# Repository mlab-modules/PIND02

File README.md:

# PIND02 - Solid-state semiconductor radiation detector

The PIN diode semiconductor detector for ionizing radiation. 

## Main features
  - sensitivity to a wide range of ionizing radiation types (charged particles, ions, photons, etc.)
  - Low-power consumtion
  - lightweight

## Basic usage

The module outputs pulses, which need to be digitized for computer processing. The suitable hardware for that task is [PCRD07](https://github.com/mlab-modules/PCRD07)

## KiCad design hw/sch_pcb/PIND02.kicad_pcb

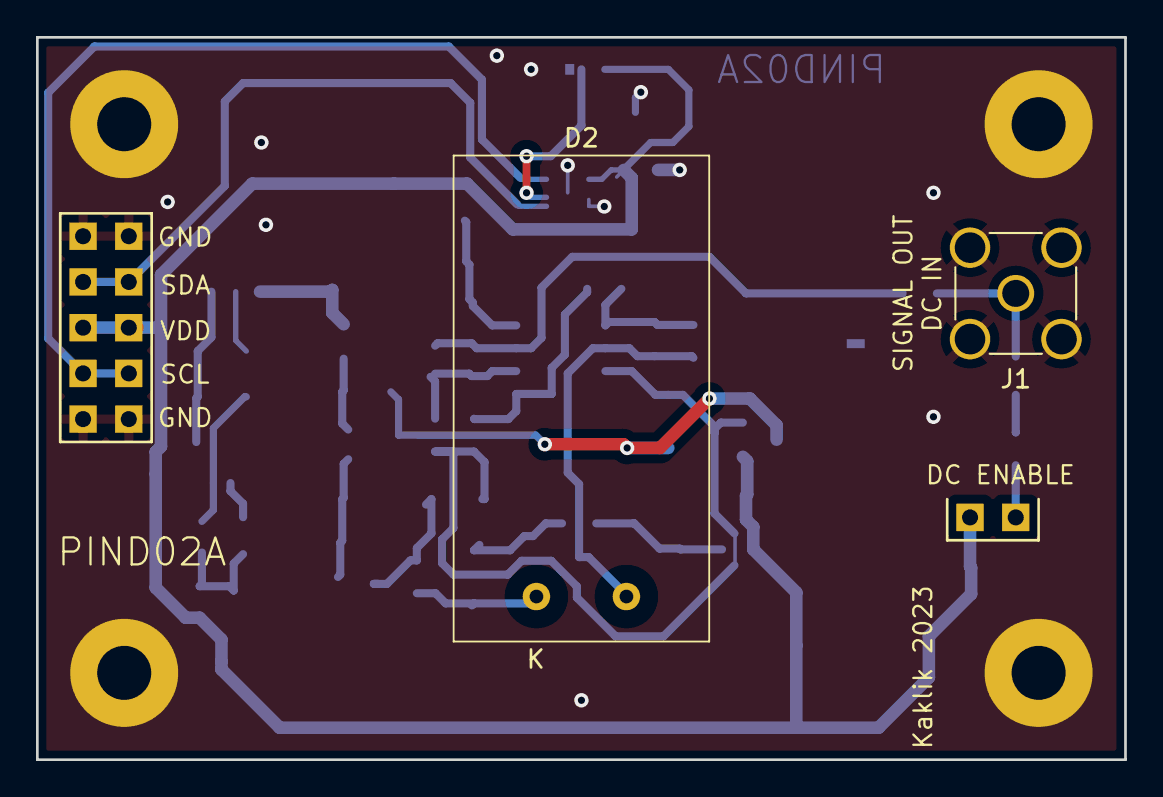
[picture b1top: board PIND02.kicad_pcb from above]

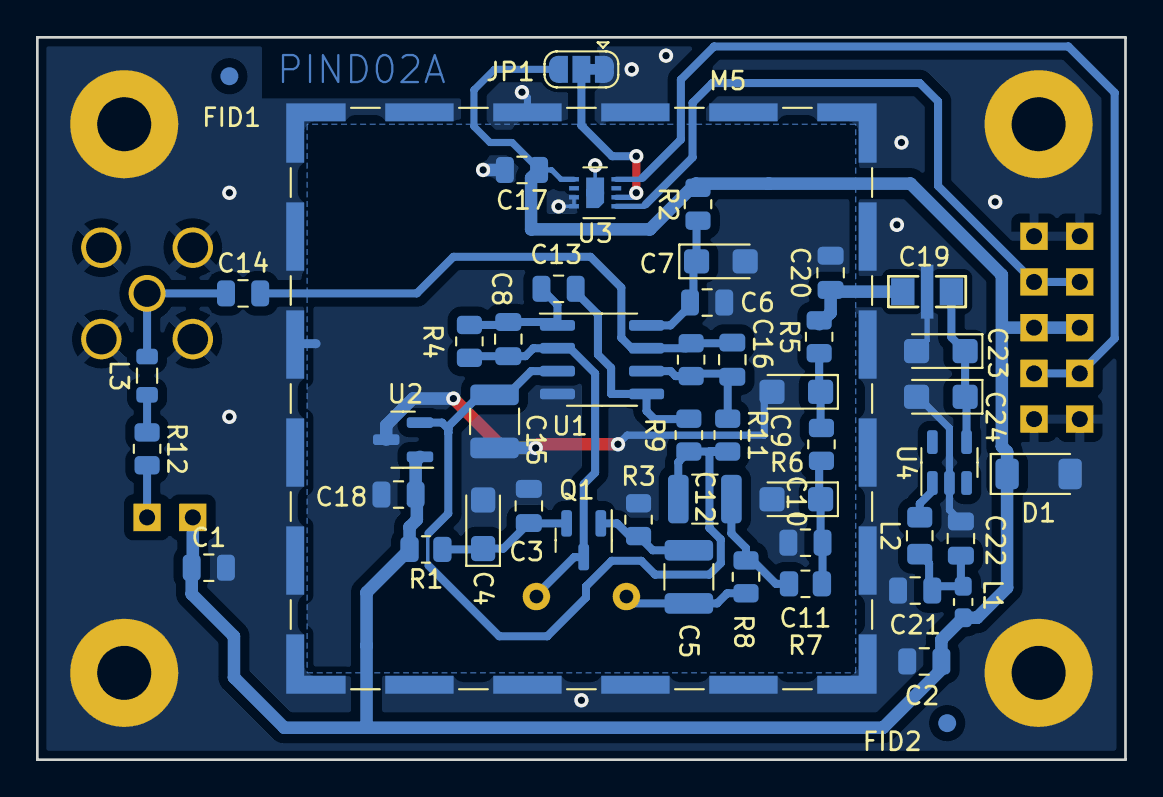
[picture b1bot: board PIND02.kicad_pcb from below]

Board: 2 copper layers, 60.5 x 40.1 mm, 58 parts (50 on the bottom side), 26 nets.

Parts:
C1, C21: 10uF; C_0805_2012Metric
C2, C3, C6, C11, C13, C14, C17, C18, C20, C22: 100nF; C_0805_2012Metric
C4, C7, C9, C10, C23, C24: 10uF; CP_EIA-3216-18_Kemet-A
C5, C12, C15: 1uF; C_1210_3225Metric
C8: 1pF/NP0 251R15S1R0AV4E; C_0805_2012Metric
C16: 3n3; C_0805_2012Metric
C19: NFM21PC105-1uF; FIR_0805
D1: BZV55C-6,2V; D_MiniMELF
D2: S2744-09; HAMAMATSU_S2744-09
FID1, FID2: Fiducial; Fiducial_1mm_Mask2mm
J1: Conn_Coaxial; SMA_Amphenol_901-144_Vertical
J2: MLAB I2C interface; Straight_2x05
J3: HEADER_2x01; Straight_2x01
JP1: Address select; SolderJumper-3_P1.3mm_Bridged12_RoundedPad1.0x1.5mm
JP2: Jumper_2_Bridged; NetTie-2_SMD_Pad0.5mm
L1: NL03KT330; L_0603_1608Metric_Pad1.05x0.95mm_HandSolder
L2: DFE252012P-4R7M; L_0805_2012Metric_Pad1.15x1.40mm_HandSolder
L3: L; L_0805_2012Metric
M1, M2: HOLE M3; MountingHole_3mm
M3, M4: HOLE; MountingHole_3mm
M5: RFShield_TwoPieces; Laird_Technologies_BMI-S-204-F_32.00x32.00mm
Q1: 2SK2394-6; SOT-23
R1, R2: 470R; R_0805_2012Metric
R3, R5, R6, R7, R8, R10: 4k7; R_0805_2012Metric
R4: 10M; R_0805_2012Metric
R9: 10k; R_0805_2012Metric
R11: 1k; R_0805_2012Metric
R12: 100; R_0805_2012Metric
U1: OPA2314; SOIC-8_3.9x4.9mm_P1.27mm
U2: ISL21080DIH312Z-TK; SOT-23
U3: SHT31-DIS; Sensirion_DFN-8-1EP_2.5x2.5mm_P0.5mm_EP1.1x1.7mm
U4: TPS613222ADBV; SOT-23-5

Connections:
+5V: C19.3, C20.1, R5.2
/A: C8.2, D2.2 (A), Q1.3 (G), R4.2, U1.2 (-)
/K: C5.2, D2.1 (K), R8.1
/REF: C12.2, C15.1, R9.1, R11.2, U1.3 (+), U2.2 (Vout)
GND: C1.2, C2.2, C17.2, C19.2, C21.2, C22.2, C23.2, C24.2, D1.2 (A), J1.2 (Ext), J2.1, J2.2, J2.9, J2.10, JP1.1 (A), JP2.2, M1.1, M2.1, M3.1, M4.1, M5.1 (Shield), U3.7 (R), U3.8 (VSS), U3.9 (VSS), U4.2 (GND)
GNDA: C3.2, C4.2, C6.2, C7.2, C9.2, C10.2, C11.2, C15.2, C18.2, C20.2, JP2.1, R3.2, U1.4 (V-), U2.3 (GND)
unnamed: C9.1, R5.1, R6.2
unnamed: C10.1, C11.1, R6.1, R7.2
unnamed: C12.1, R7.1, R8.2
unnamed: C8.1, C13.2, R4.1, U1.1
unnamed: C14.2, C16.1, R10.1, U1.7
unnamed: C21.1, C22.1, L1.2, L2.1
unnamed: C14.1, J1.1 (In), L3.2
unnamed: J3.2, R12.2
unnamed: JP1.2 (C), U3.2 (ADDR)
unnamed: L3.1, R12.1
unnamed: C3.1, C4.1, Q1.2 (D), R1.1
unnamed: C5.1, Q1.1 (S), R3.1
unnamed: C13.1, R9.2, U1.5 (+)
unnamed: C16.2, R10.2, R11.1, U1.6 (-)
unnamed: C6.1, C7.1, R2.1, U1.8 (V+)
unnamed: J2.7, J2.8, U3.4 (SCL)
unnamed: J2.3, J2.4, U3.1 (SDA)
unnamed: L2.2, U4.1 (SW)
unnamed: C19.1, C23.1, C24.1, U4.4 (VOUT)
VDD: C1.1, C2.1, C17.1, C18.1, D1.1 (K), J2.5, J2.6, J3.1, JP1.3 (B), L1.1, R1.2, R2.2, U2.1 (Vin), U3.5 (VDD)

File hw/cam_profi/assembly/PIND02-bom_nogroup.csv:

Component,Description,Part,References,Value,Footprint,Quantity Per PCB,Datasheet,ust_id
1,Unpolarized capacitor,C,C16,3n3,C_0603_1608Metric,1,~,628d0fc8dc56076e9a223574
2,Unpolarized capacitor,C,C3C6C11C13C14C18,100nF,C_0603_1608Metric,6,~,5c70984812875079b91f8bf2
3,,C_Small-Device-ISM02A-rescue,C2C17,100nF,C_0805_2012Metric,2,,5c70984812875079b91f8bf2
4,,C-device-DATALOGGER01A-rescue-CCP2019V01A-rescue,C20C22,100nF,C_0603_1608Metric,2,,5c70984812875079b91f8bf2
5,Unpolarized capacitor,C,C5C12C15,1uF,C_0603_1608Metric,3,~,643f03ef76c82a1d3b576bed
6,,C_Small-Device-ISM02A-rescue,C1,10uF,C_0805_2012Metric,1,,5c70984812875079b91f8bbe
7,Unpolarized capacitor,C,C4C7C9C10C21,10uF,C_0603_1608Metric,5,~,643f075476c82a1d3b576c19
8,,C-device-DATALOGGER01A-rescue-CCP2019V01A-rescue,C23C24,10uF,C_0603_1608Metric,2,,643f075476c82a1d3b576c19
9,Unpolarized capacitor,C,C8,1pF/NP0 251R15S1R0AV4E,C_0805_2012Metric,1,~,5c70984712875079b91f8b9f
10,,EMI_Filter_C-device-DATALOGGER01A-rescue-CCP2019V01A-rescue,C19,NFM21PC105-1uF,FIR_0805,1,http://www.murata.com/~/media/webrenewal/support/library/cat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,5c70984412875079b91f880f
11,,D_ZENER-MLAB_D,D1,"BZV55C-5,6V",D_SMA,1,,5c70984512875079b91f88b2
12,Photodiode,D_Photo,D2,S2744-09,HAMAMATSU_S2744-09,1,https://www.hamamatsu.com/content/dam/hamamatsu-photonics/si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,628d118cdc56076e9a2235e4
13,"coaxial connector (BNC, SMA, SMB, SMC, Cinch/RCA, LEMO, ...)",Conn_Coaxial,J1,Conn_Coaxial,,1, ~,
14,2x01 2.54 mm pitch header,HEADER_2x01,J3,HEADER_2x01,,1,,
15,"2x05 2.54 mm pitch header, 2 pins next to each other are connected",HEADER_2x05_PARALLEL,J2,HEADER_2x05_PARALLEL,,1,,
16,"Inductor, small symbol",L_Small,L2,DFE252012P-4R7M,L_0805_2012Metric_Pad1.15x1.40mm_HandSolder,1,~,5cc3309d128750448e54e8d8
17,Inductor,L,L3,L,,1,~,
18,"Inductor with ferrite core, small symbol",L_Ferrite_Small,L1,NL03KT330,L_0603_1608Metric_Pad1.05x0.95mm_HandSolder,1,~,64fe1808f3b9d36f37fc944d
19,"N-JFET transistor, source/drain/gate",Q_NJFET_SDG,Q1,2SK2394-6,SOT-23,1,~,628d134fdc56076e9a223625
20,Resistor,R,R12,100,SMD-0805,1,~,5c70984512875079b91f8977
21,Resistor,R,R1R2,470R,R_0603_1608Metric,2,~,5c70984512875079b91f8959
22,Resistor,R,R11,1k,R_0603_1608Metric,1,~,5c70984512875079b91f895c
23,Resistor,R,R3R5R6R7R8R10,4k7,R_0603_1608Metric,6,~,5c70984512875079b91f8960
24,Resistor,R,R9,10k,R_0603_1608Metric,1,~,5c70984512875079b91f8962
25,Resistor,R,R4,10M,R_0603_1608Metric,1,~,5c70984712875079b91f8b6d
26,"2.0V 25μA Micropower Voltage Reference, SOT-23",ISL21070CIH320Z-TK,U2,ISL21080DIH312Z-TK,SOT-23,1,https://cz.mouser.com/datasheet/2/698/REN_isl21080_DST_20040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,5c70984712875079b91f8b7a
27,Op amp.,AD8692_1,U1,OPA2314,SOIC-8_3.9x4.9mm_P1.27mm,1,https://www.ti.com/lit/ds/symlink/opa2314.pdf,5c70984412875079b91f879b
28,"I²C humidity and temperature sensor, ±2%RH, ±0.2°C, DFN-8",SHT31-DIS,U3,SHT31-DIS,Sensirion_DFN-8-1EP_2.5x2.5mm_P0.5mm_EP1.1x1.7mm,1,https://sensirion.com/media/documents/213E6A3B/63A5A569/Data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,
29,"1.8A Step-Up Converter, 5V Output Voltage, 0.9-5.5V Input Voltage, SOT-23-5",TPS613222ADBV,U4,TPS613222ADBV,SOT-23-5,1,http://www.ti.com/lit/ds/symlink/tps61322.pdf,5c7190ae1287500b4e112e04

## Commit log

2023-09-10 Update metadata files
2023-09-10 Initial schematics of PIN semiconductor ionising radiation sensor.
2023-09-10 Add KiCAD processing GitHub workflow.
2023-09-10 Update actions products
2023-09-10 Update title block Resolve ERC errors.
2023-09-11 Update workflow files
2023-09-16 Update status
2023-09-24 Assing footprints to components. Starting of PCB design.
2023-09-24 PCB design WIP.
2023-09-25 The first fully routed PCB.
2023-09-25 Add silcreen texts.
2023-09-26 Add board dimensions.
2023-09-26 Improve protection diode type and footprint.
2023-09-26 Routed PCB.
2023-09-27 Add solder mask keepout zone. Resolve #1.
2023-09-27 Kontrola a upravy pred vyrobou
2023-10-02 Edit UST_ID
2023-10-04 Edit B.Fab
2023-10-11 Adding the sensor frame design.
2023-10-16 Increase gain.
2023-10-21 Add a photo of module.
2023-10-22 Cover sensing area with one printed layer.
2023-11-12 Update measured values.
2023-12-08 Set layer height to 0.2mm.
